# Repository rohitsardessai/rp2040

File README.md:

# RP2040 Breakout board

Breakout board for the RP2040 microcontroller with minimal circuitry.
The repository contains Eagle board files and libraries.

Features:
- 4 Layer board stackup (sig-gnd-pwr-sig)
- 55mm x 25mm
- RP2040
- USB-C interface (90 Ohm differential impedance)
- MPU9250 9 DoF IMU
- User button and LED
- Castellated pads

This board was made by referring to Philip Salmony's wonderful [YouTube channel](https://www.youtube.com/c/PhilS94/videos) . I highly recommend it.
Sparkfun's open source designs also helped a lot.

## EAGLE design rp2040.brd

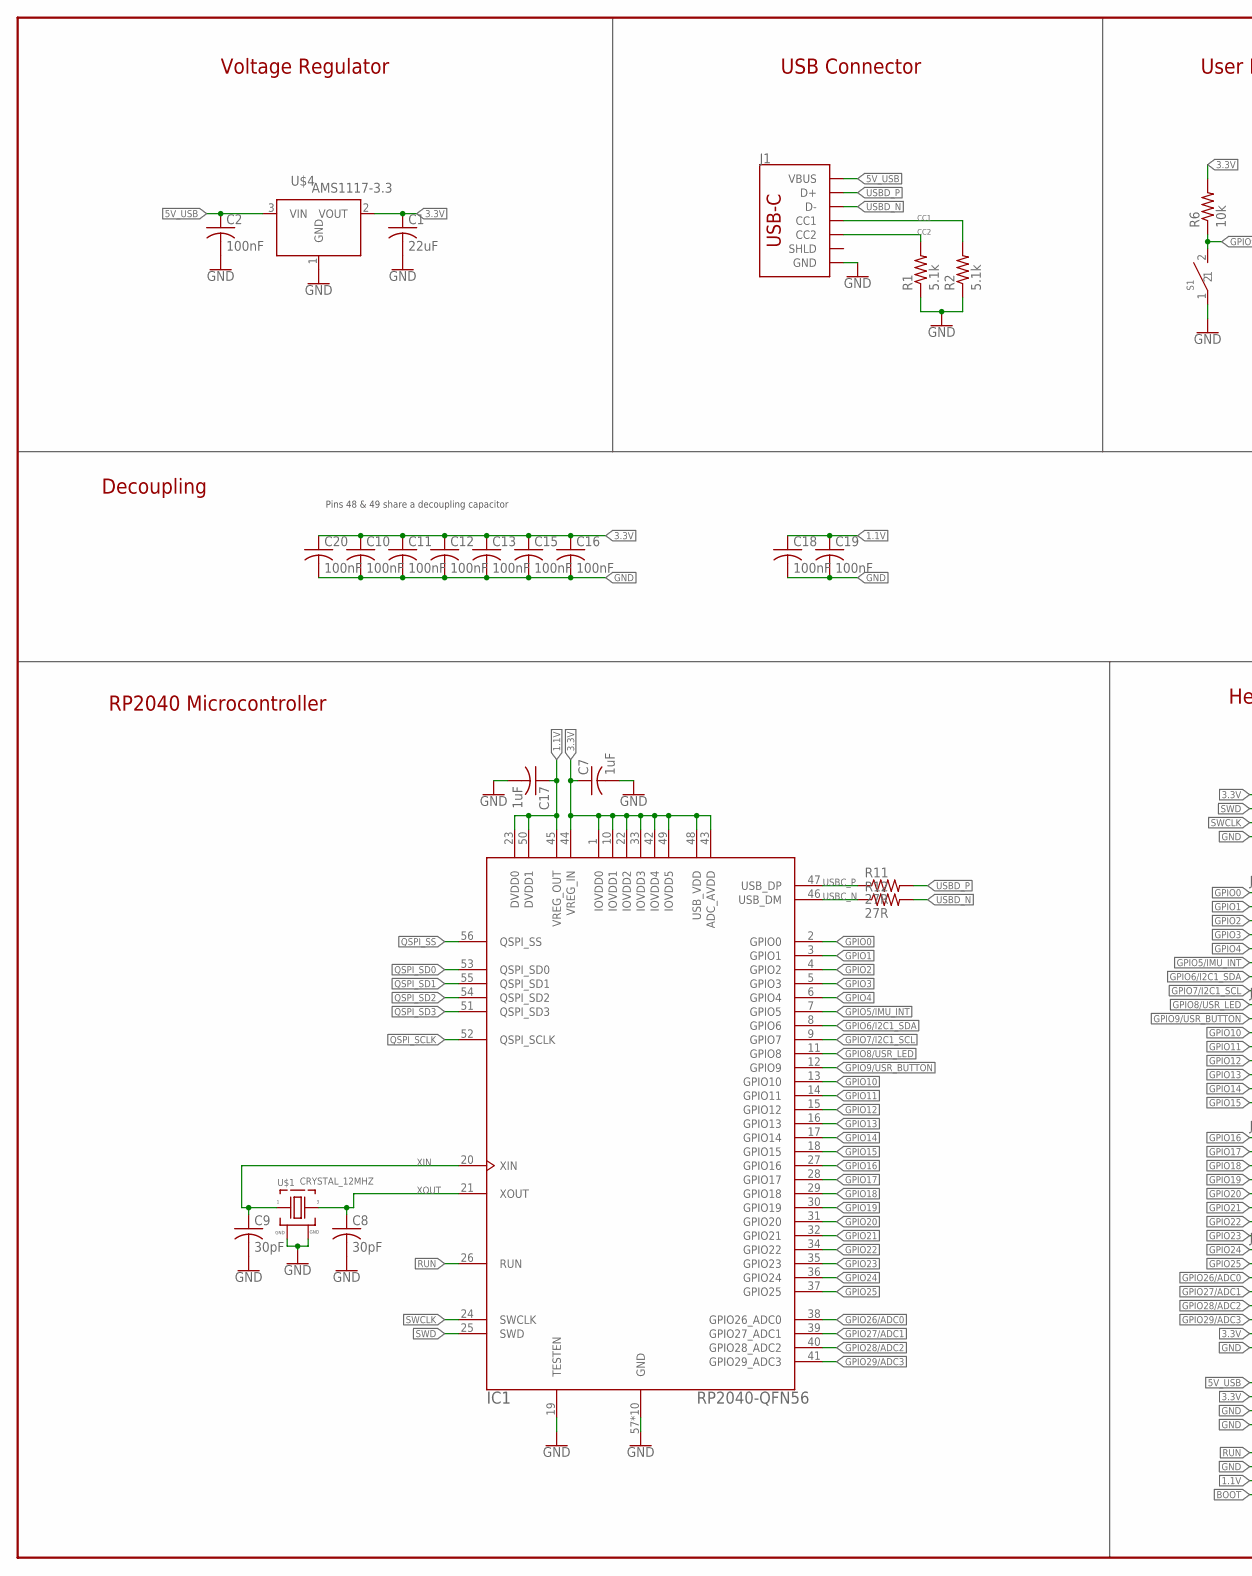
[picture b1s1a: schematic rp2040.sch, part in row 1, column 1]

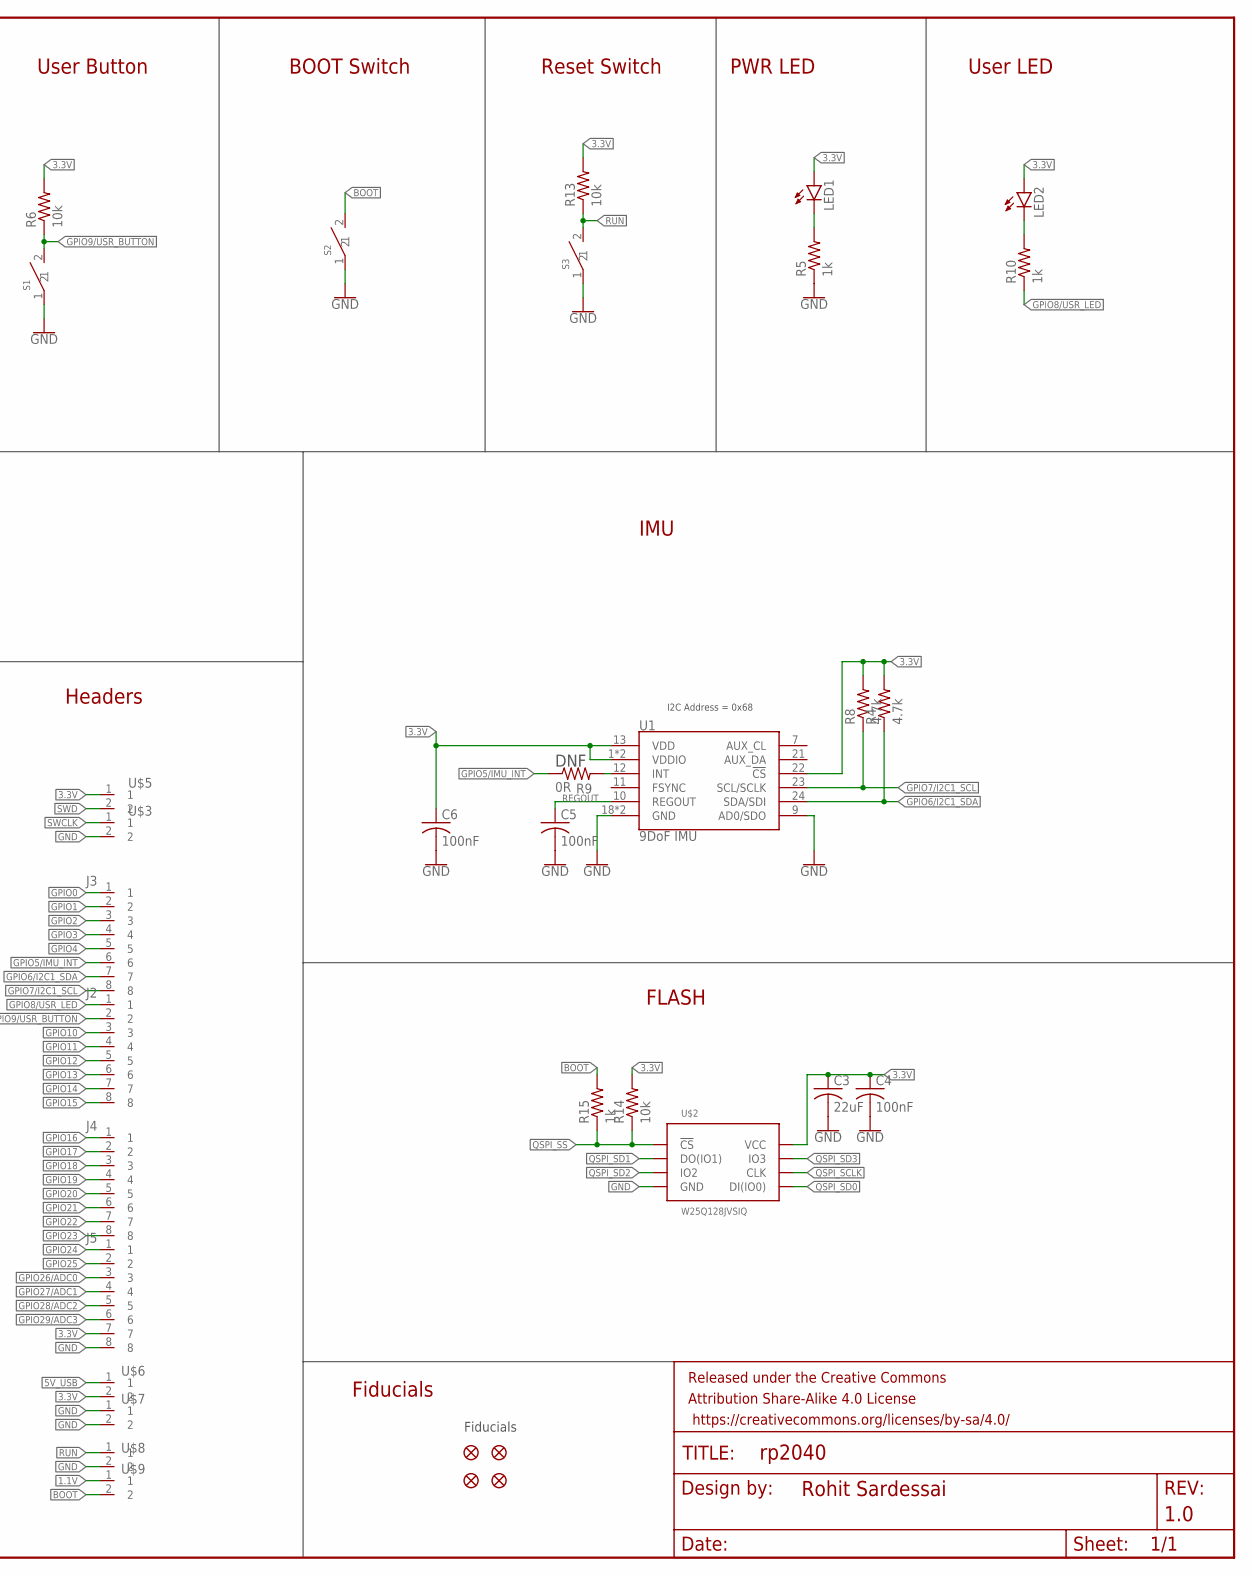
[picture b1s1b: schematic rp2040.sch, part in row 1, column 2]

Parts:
C1: 22uF; C0603
C2: 100nF; C0603
C3: 22uF; C0402
C4, C5, C6, C10, C11, C12, C13, C15, C16, C18, C19, C20: 100nF; C0402
C7, C17: 1uF; C0402
C8, C9: 30pF; C0402
FD1, FD2, FD3, FD4: FIDUCIAL1X2; FIDUCIAL-1X2
FRAME1: FRAME-LEDGERNO_FOOTPRINT; DUMMY
IC1: RP2040-QFN56; RP2040-QFN-56
J1: USB_C_4-LAYER_PADS; USB-C-16P_4LAYER-PADS
J2, J3, J4, J5: 1X6_2.5MM; 1X06_2.5MM
LED1, LED2: LEDCHIPLED_0603; CHIPLED_0603
R1, R2: 5.1k; R0402
R4, R8: 4.7k; R0402
R5, R10, R15: 1k; R0402
R6, R13, R14: 10k; R0402
R9: 0R; R0402
R11, R12: 27R; R0402
S1, S2, S3: TS-1088-AR02016; PUSH_SW_SMD
U1: 9DoF IMU; QFN24-3X3
U$1: CRYSTAL_12MHZ
U$2: W25Q128JVSIQ; SOIC8-208MIL
U$3, U$5, U$6, U$7, U$8, U$9: 1X2_2.5MM; 1X02_2.5MM
U$4: AMS1117-3.3; SOT-223

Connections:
1.1V: C17.1, C18.1, C19.1, IC1.23 (DVDD0), IC1.45 (VREG_OUT), IC1.50 (DVDD1), U$9.1
3.3V: C1.1, C3.1, C4.1, C6.1, C7.1, C10.1, C11.1, C12.1, C13.1, C15.1, C16.1, C20.1, IC1.1 (IOVDD0), IC1.10 (IOVDD1), IC1.22 (IOVDD2), IC1.33 (IOVDD3), IC1.42 (IOVDD4), IC1.43 (ADC_AVDD), IC1.44 (VREG_IN), IC1.48 (USB_VDD), IC1.49 (IOVDD5), J5.7, LED1.A, LED2.A, R4.2, R6.2, R8.2, R13.2, R14.2, U1.1 (VDDIO), U1.8 (VDDIO), U1.13 (VDD), U1.22 (!CS), U$2.8 (VCC), U$4.2 (VOUT), U$5.1, U$6.2
5V_USB: C2.1, J1.VBUS1 (VBUS), J1.VBUS2 (VBUS), U$4.3 (VIN), U$6.1
BOOT: R15.2, S2.2, U$9.2
CC1: J1.A5 (CC1), R2.2
CC2: J1.B5 (CC2), R1.2
GND: C1.2, C2.2, C3.2, C4.2, C5.2, C6.2, C7.2, C8.2, C9.2, C10.2, C11.2, C12.2, C13.2, C15.2, C16.2, C17.2, C18.2, C19.2, C20.2, IC1.19 (TESTEN), IC1.57 (GND), IC1.58 (GND), IC1.59 (GND), IC1.60 (GND), IC1.61 (GND), IC1.62 (GND), IC1.63 (GND), IC1.64 (GND), IC1.65 (GND), IC1.66 (GND), J1.GND, J1.GND2 (GND), J5.8, R1.1, R2.1, R5.1, S1.1, S2.1, S3.1, U1.9 (AD0/SDO), U1.18 (GND), U1.20 (GND), U$1.2 (GND), U$1.4 (GND), U$2.4 (GND), U$3.2, U$4.1 (GND), U$7.1, U$7.2, U$8.2
GPIO0: IC1.2 (GPIO0), J3.1
GPIO1: IC1.3 (GPIO1), J3.2
GPIO2: IC1.4 (GPIO2), J3.3
GPIO3: IC1.5 (GPIO3), J3.4
GPIO4: IC1.6 (GPIO4), J3.5
GPIO5/IMU_INT: IC1.7 (GPIO5), J3.6, R9.1
GPIO6/I2C1_SDA: IC1.8 (GPIO6), J3.7, R4.1, U1.24 (SDA/SDI)
GPIO7/I2C1_SCL: IC1.9 (GPIO7), J3.8, R8.1, U1.23 (SCL/SCLK)
GPIO8/USR_LED: IC1.11 (GPIO8), J2.1, R10.1
GPIO9/USR_BUTTON: IC1.12 (GPIO9), J2.2, R6.1, S1.2
GPIO10: IC1.13 (GPIO10), J2.3
GPIO11: IC1.14 (GPIO11), J2.4
GPIO12: IC1.15 (GPIO12), J2.5
GPIO13: IC1.16 (GPIO13), J2.6
GPIO14: IC1.17 (GPIO14), J2.7
GPIO15: IC1.18 (GPIO15), J2.8
GPIO16: IC1.27 (GPIO16), J4.1
GPIO17: IC1.28 (GPIO17), J4.2
GPIO18: IC1.29 (GPIO18), J4.3
GPIO19: IC1.30 (GPIO19), J4.4
GPIO20: IC1.31 (GPIO20), J4.5
GPIO21: IC1.32 (GPIO21), J4.6
GPIO22: IC1.34 (GPIO22), J4.7
GPIO23: IC1.35 (GPIO23), J4.8
GPIO24: IC1.36 (GPIO24), J5.1
GPIO25: IC1.37 (GPIO25), J5.2
GPIO26/ADC0: IC1.38 (GPIO26_ADC0), J5.3
GPIO27/ADC1: IC1.39 (GPIO27_ADC1), J5.4
GPIO28/ADC2: IC1.40 (GPIO28_ADC2), J5.5
GPIO29/ADC3: IC1.41 (GPIO29_ADC3), J5.6
unnamed: LED1.C, R5.2
unnamed: R9.2, U1.12 (INT)
unnamed: LED2.C, R10.2
QSPI_SCLK: IC1.52 (QSPI_SCLK), U$2.6 (CLK)
QSPI_SD0: IC1.53 (QSPI_SD0), U$2.5 (DI(IO0))
QSPI_SD1: IC1.55 (QSPI_SD1), U$2.2 (DO(IO1))
QSPI_SD2: IC1.54 (QSPI_SD2), U$2.3 (IO2)
QSPI_SD3: IC1.51 (QSPI_SD3), U$2.7 (IO3)
QSPI_SS: IC1.56 (QSPI_SS), R14.1, R15.1, U$2.1 (!CS)
REGOUT: C5.1, U1.10 (REGOUT)
RUN: IC1.26 (RUN), R13.1, S3.2, U$8.1
SWCLK: IC1.24 (SWCLK), U$3.1
SWD: IC1.25 (SWD), U$5.2
USBC_N: IC1.46 (USB_DM), R12.1
USBC_P: IC1.47 (USB_DP), R11.1
USBD_N: J1.A7 (D-), J1.B7 (D-), R12.2
USBD_P: J1.A6 (D+), J1.B6 (D+), R11.2
XIN: C9.1, IC1.20 (XIN), U$1.1
XOUT: C8.1, IC1.21 (XOUT), U$1.3

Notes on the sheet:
Fiducials
DNF
I2C Address = 0x68
Voltage Regulator
USB Connector
User Button
BOOT Switch
PWR LED
User LED
IMU
FLASH
RP2040 Microcontroller
Decoupling
Reset Switch
Headers
Pins 48 & 49 share a decoupling capacitor

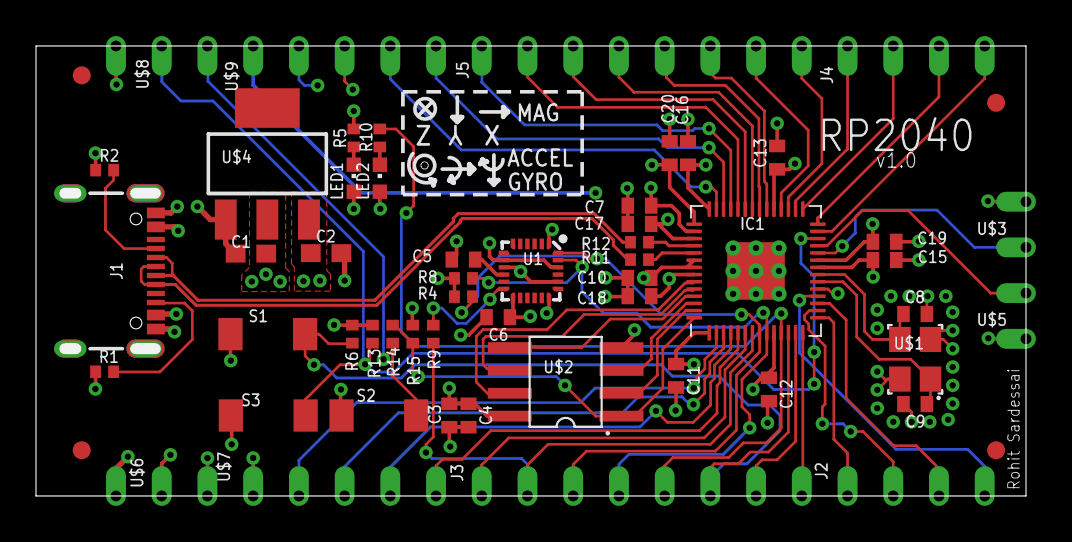
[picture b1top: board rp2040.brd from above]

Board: 4 copper layers, 55.0 x 25.0 mm, 58 parts (0 on the bottom side), 56 nets.

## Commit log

2021-08-09 initial board, without final silkscreen
2021-08-11 added bottom silk
2021-08-11 added top & bottom silk
2021-08-11 improved traces, reduced vias

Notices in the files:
parts and their libraries:
SparkFun-Connectors: Licensing: Creative Commons ShareAlike 4.0 International - https://creativecommons.org/licenses/by-sa/4.0
SparkFun-Aesthetics: Released under the Creative Commons Attribution Share-Alike 4.0 License
SparkFun-Aesthetics: https://creativecommons.org/licenses/by-sa/4.0
